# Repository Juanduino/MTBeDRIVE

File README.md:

# MTBeDRIVE

This is a eMTB motor-controller hardware repository. The concept is a uniform powerstage, with a standardized MCU pinmap.
The goal is to make a modular controller, which is able to easily swap bulk capacitors. Having the MCU (Micro Controller/Drivers/Step_down etc.) 
on a seperate layer from the powerstage, optimizes and focuses the cooling on the powerstage, being directly attached to a heatsink. 

The 1.3mm x 3mm copper busbar can carry around 75 amp´s and has a resistance of 0.3mOhm, plus the outer layer copper (105um) with a resistance of around 1.5mOhm. The outer layer trace, alone, can carry around 25amp´s. 

*

The Phase wires on the intended 6368 sensored BLDC are AWG12. If you plit a AWG12 into two, it roughly corrosponds to two AWG16 wires, which fit on the XT30 connector. XT30 connector should handle burst current´s ower 30 amp. 

You can say, the design seek´s a slim and compackt expresion, becource it is specifically designed with a MTB conversion in mind.

*

Specifically the interface is designed with the Portenta H7 (Dual Core MCU) in mind, but other MCU´s could equally connect with the powerstage.'
For the erly_design, at this stage, the Portenta H7 is the only available choice for development on STM32H747. Later when the MCU´s emerges in stock, we can combine the Portenta H7 and driver/step_down layer in a custom PCB design. 

*

Becouse the bulk capacitors has a limited lifetime, the overall system lifetime can be extended by detaching the bulk capacitor "bank". By making it modular, it can also vary en size. 

*

There are many kinds of MOSFETS footprint´s, some with better propaties then other. Having a BASE design, with uniform dimensions and interface, makes it possible to reuse the independent parts, which can then later realign with other shapes. 

*

The Firmware for the field oriented control (commutation for 3 phase BLDC) is based on SimpleFOC https://github.com/simplefoc

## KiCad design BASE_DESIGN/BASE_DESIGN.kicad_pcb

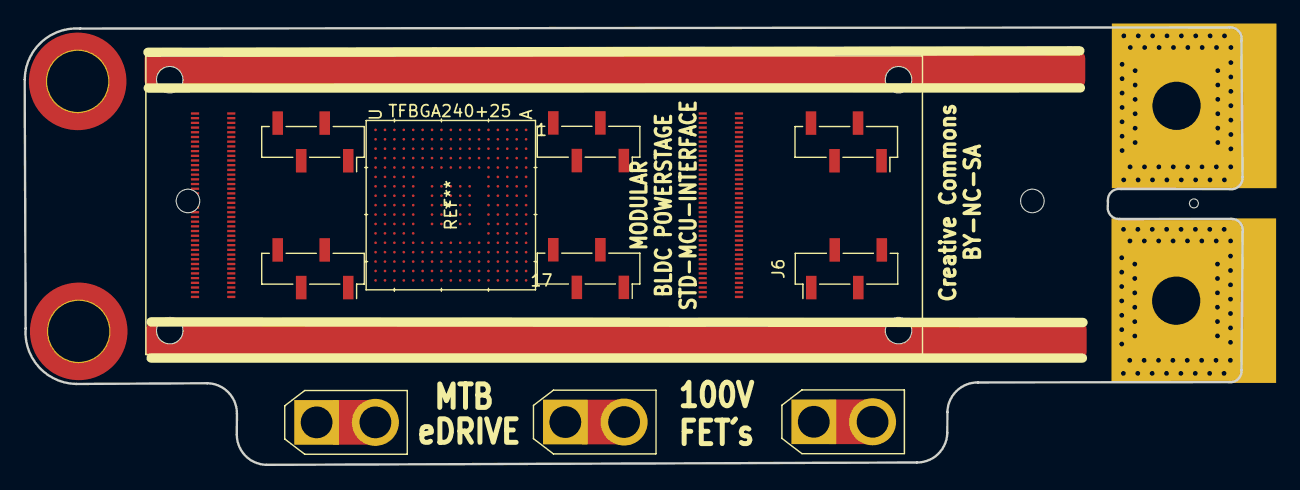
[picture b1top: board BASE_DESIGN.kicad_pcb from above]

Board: 2 copper layers, 103.6 x 37.2 mm, 6 parts (0 on the bottom side), 3 nets, no tracks yet.

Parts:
J1, J2, J3, J4, J5: PinSocket_1x04_P2.00mm_Vertical_SMD_Pin1Right
J6: PinSocket_1x04_P2.00mm_Vertical_SMD_Pin1Left

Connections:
3.3v: J4.4, J5.4, J6.1
ANA_OUT2: J5.3, J6.3
GND2: J4.2, J5.3, J6.2

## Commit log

2022-07-11 Add files via upload
    Added CC
2022-07-11 Img added
    Added images
2022-07-11 Added BASE design
    Dimensions are locked.
2022-07-11 Changelog
2022-07-11 Added BASE portenta stack
2022-07-11 Aded BASE_MODULAR
2022-07-11 Updade
2022-07-12 Front
2022-07-12 Moved XT30 connectors 1mm
2022-07-13 Added Portenta Pinout
2022-07-13 Added wire points for CAN and HALL´s
2022-07-13 Moved Portenta for CAN and Hall wire
2022-07-13 Moved header
2022-07-13 Aligned

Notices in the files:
BASE_DESIGN/BASE_DESIGN.kicad_pcb:
Creative Commons
BY-NC-SA
parts and their libraries:
Copyright 2021 Accelerated Designs. All rights reserved.
